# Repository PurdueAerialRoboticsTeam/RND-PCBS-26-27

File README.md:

2026-27 Git Repo for RND PCB designs. 25-26 reference designs available in archive

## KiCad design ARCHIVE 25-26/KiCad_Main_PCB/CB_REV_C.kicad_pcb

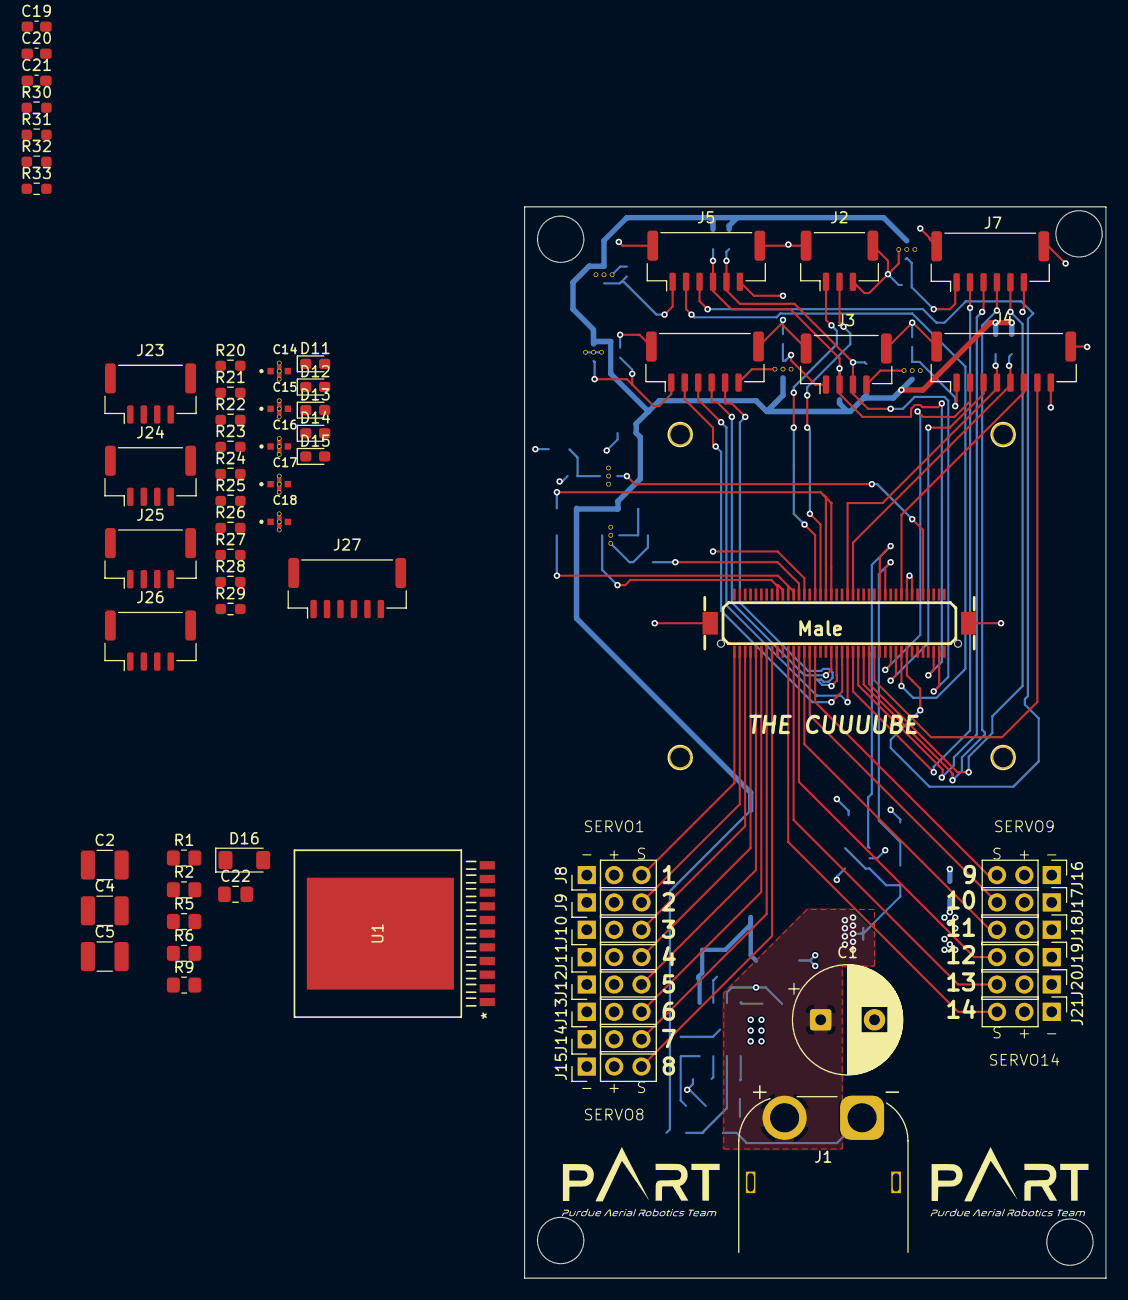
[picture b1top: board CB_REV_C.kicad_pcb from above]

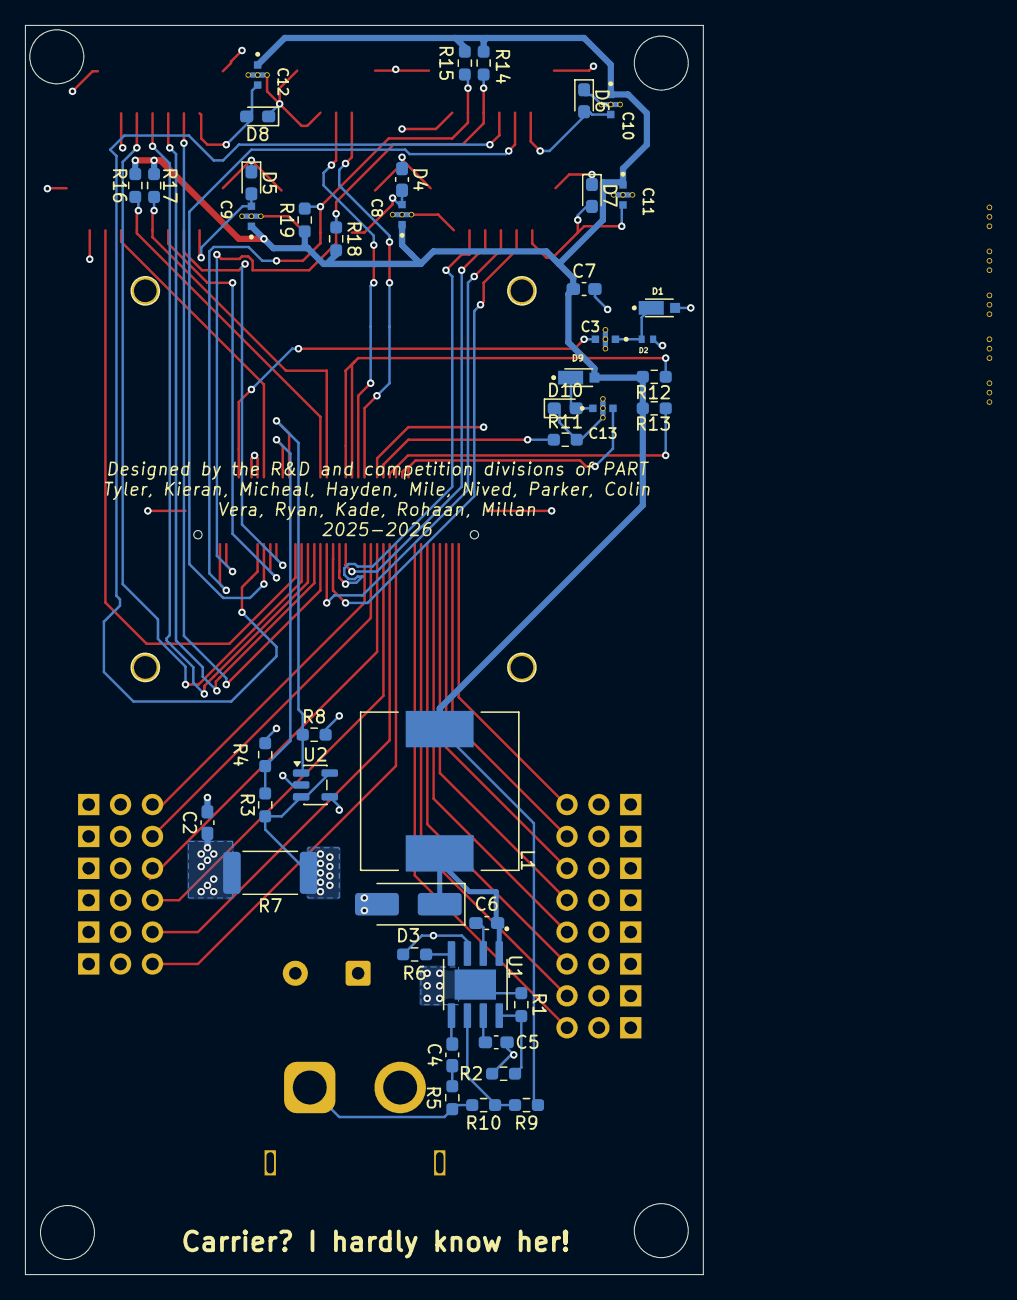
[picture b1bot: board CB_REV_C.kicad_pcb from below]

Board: 4 copper layers, 54.0 x 99.5 mm, 110 parts (44 on the bottom side), 70 nets.

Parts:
C1: 470u; CP_Radial_D10.0mm_P5.00mm
C2, C4, C5: 10uF; C_1210_3225Metric_Pad1.33x2.70mm_HandSolder
C2#2, C7: 10u; C_0603_1608Metric_Pad1.08x0.95mm_HandSolder
C3, C8, C9, C10, C11, C12, C13, C14, C15, C16, C17, C18: NFM18PC104R1C3D; FIL_NFM18PC104R1C3D
C4#2: 3n; C_0603_1608Metric_Pad1.08x0.95mm_HandSolder
C5#2, C6: 0.1u; C_0603_1608Metric_Pad1.08x0.95mm_HandSolder
C19, C20: 10uF 6.22 mOhm; C_0603_1608Metric_Pad1.08x0.95mm_HandSolder
C21: 47uF 2mOhm; C_0603_1608Metric_Pad1.08x0.95mm_HandSolder
C22: 0.47uF; C_0805_2012Metric_Pad1.18x1.45mm_HandSolder
D1, D9: MSS1P4-M3; MSS1P4-M3_89A
D2: PESD0603-240; PESD0402-140
D3: SS54; D_SMA_Handsoldering
D4: PESD0603-240; C_0603_1608Metric_Pad1.08x0.95mm_HandSolder
D5, D6, D7, D8, D11, D12, D13, D14, D15: PESD0603-240; D_0603_1608Metric_Pad1.05x0.95mm_HandSolder
D10: PESD0402-140; D_0603_1608Metric_Pad1.05x0.95mm_HandSolder
D16: BZV55B4V7; D_MiniMELF
J1: XT60; AMASS_XT60PW-M_1x02_P7.20mm_Horizontal
J2: Conn_01x03; JST_GH_BM03B-GHS-TBT_1x03-1MP_P1.25mm_Vertical
J3, J23, J24, J25, J26: Conn_01x04_MountingPin; JST_GH_BM04B-GHS-TBT_1x04-1MP_P1.25mm_Vertical
J4: Conn_01x08_MountingPin; JST_GH_BM08B-GHS-TBT_1x08-1MP_P1.25mm_Vertical
J5, J6, J7, J27: Conn_01x06_MountingPin; JST_GH_BM06B-GHS-TBT_1x06-1MP_P1.25mm_Vertical
J8, J9, J10, J11, J12, J13, J14, J15, J16, J17, J18, J19, J20, J21: Conn_01x03_Pin; PinHeader_1x03_P2.54mm_Vertical
J22: Cube80Pin; CON-DF17-80M
L1: 22u; L_12x12mm_H8mm
R1: 33 kOhm; R_0805_2012Metric_Pad1.20x1.40mm_HandSolder
R1#2, R2#2: 47k; R_0603_1608Metric_Pad0.98x0.95mm_HandSolder
R2: 10 kOhm; R_0805_2012Metric_Pad1.20x1.40mm_HandSolder
R3: 82K; R_0603_1608Metric_Pad0.98x0.95mm_HandSolder
R4: 47K; R_0603_1608Metric_Pad0.98x0.95mm_HandSolder
R5: 1.3k Ohm; R_0805_2012Metric_Pad1.20x1.40mm_HandSolder
R5#2: 43.7k; R_0603_1608Metric_Pad0.98x0.95mm_HandSolder
R6: 6.8k Ohm; R_0805_2012Metric_Pad1.20x1.40mm_HandSolder
R6#2: 46.4k; R_0603_1608Metric_Pad0.98x0.95mm_HandSolder
R7: 0.01; R_2512_6332Metric_Pad1.40x3.35mm_HandSolder
R8: 75k; R_0603_1608Metric_Pad0.98x0.95mm_HandSolder
R9: 100 Ohm; R_0805_2012Metric_Pad1.20x1.40mm_HandSolder
R9#2: 52.3k; R_0603_1608Metric_Pad0.98x0.95mm_HandSolder
R10, R14, R15, R16, R17, R18, R19, R20, R21, R22, R23, R24, R25, R26, R27, R28, R29, R33: 10k; R_0603_1608Metric_Pad0.98x0.95mm_HandSolder
R11, R12, R13: 100k; R_0603_1608Metric_Pad0.98x0.95mm_HandSolder
R30: 40.2 kOhm; R_0603_1608Metric_Pad0.98x0.95mm_HandSolder
R31: 4.42 kOhm; R_0603_1608Metric_Pad0.98x0.95mm_HandSolder
R32: 1.37K; R_0603_1608Metric_Pad0.98x0.95mm_HandSolder
U1: LMZ12008TZ/NOPB; TZA11A
U1#2: AOZ1284PI; SOP127P600X170-9N
U2: INA138; SOT-23-5

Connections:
+5V_SERVO: C7.1, C8.1, C9.1, C10.1, C11.1, C12.1, C14.1, C15.1, C16.1, C17.1, C18.1, C19.2, C20.2, C21.1, C21.2, D9.2 (A), L1.2, R6.1, R9#2.1, R12.1, R13.1, R14.2, R15.1, R16.2, R17.1, R18.2, R19.1, R20.2, R21.1, R22.2, R23.1, R24.2, R25.2, R26.1, R27.1, R28.2, R29.1, R33.1, U1.10 (VOUT), U1.11 (VOUT)
+BATT: C2.1, C2#2.1, C4.1, C5.1, C19.1, C20.1, D1.2 (A), J8.2, J9.2, J10.2, J11.2, J12.2, J13.2, J14.2, J15.2, J16.2, J17.2, J18.2, J19.2, J20.2, J21.2, J22.53, R1.1, R1#2.1, R7.2, U1.1 (VIN), U1.2 (VIN), U1#2.9 (VIN), U2.4 (-)
/80_Pin/FMU_CH1_PROT: J16.3, J22.50
/80_Pin/FMU_CH2_PROT: J17.3, J22.52
/80_Pin/FMU_CH3_PROT: J18.3, J22.54
/80_Pin/FMU_CH4_PROT: J19.3, J22.56
/80_Pin/FMU_CH5_PROT: J20.3, J22.58
/80_Pin/FMU_CH6_PROT: J21.3, J22.60
/80_Pin/IO_CH1_PROT: J8.3, J22.80
/80_Pin/IO_CH2_PROT: J9.3, J22.78
/80_Pin/IO_CH3_PROT: J10.3, J22.76
/80_Pin/IO_CH4_PROT: J11.3, J22.74
/80_Pin/IO_CH5_PROT: J12.3, J22.72
/80_Pin/IO_CH6_PROT: J13.3, J22.70
/80_Pin/IO_CH7_PROT: J14.3, J22.68
/80_Pin/IO_CH8_PROT: J15.3, J22.66
/80_Pin/VBUS_VALID: J22.57, J22.59, R13.2
/80_Pin/VDD_5V_HIPOWER_OC: J22.43, J22.45, R12.2
/80_Pin/VDD_5V_IN_PROT: C13.3, J22.61, J22.63
/80_Pin/VDD_BRICK_VALID: J22.55, R11.1
/BATT_MOT_A_MEAS: J2.1, J22.49
/BATT_MOT_V_MEAS: J2.2, J22.47
/BATT_SERVO_A_MEAS: J22.25, R8.1, U2.1
/BATT_SERVO_V_MEAS: J22.23, R3.2, R4.2
/I2C_1_SCL: J4.4, J22.37, J23.2, J24.2, J27.4, R16.1, R20.1, R22.1, R28.1
/I2C_1_SDA: J4.5, J22.35, J23.3, J24.3, J27.5, R17.2, R21.2, R23.2, R29.2
/I2C_2_SCL: J3.2, J5.4, J22.6, J25.2, J26.2, R14.1, R18.1, R24.1, R25.1
/I2C_2_SDA: J3.3, J5.5, J22.4, J25.3, J26.3, R15.2, R19.2, R26.2, R27.2
/SAFETY: J4.6, J22.17
/SERIAL1_CTS: J6.4, J22.44
/SERIAL1_RTS: J6.5, J22.42
/SERIAL1_RX: J6.3, J22.38
/SERIAL1_TX: J6.2, J22.40
/SERIAL2_CTS: J7.4, J22.32
/SERIAL2_RTS: J7.5, J22.30
/SERIAL2_RX: J7.3, J22.34
/SERIAL2_TX: J7.2, J22.36
/SERIAL3_RX: J4.3, J22.20
/SERIAL3_TX: J4.2, J22.22
/SERIAL4_RX: J5.3, J22.16
/SERIAL4_TX: J5.2, J22.18
/SERIAL5_RX: J22.12, J27.3
/SERIAL5_TX: J22.14, J27.2
/VDD_SERVO_IN: C3.3, J22.9
/~IO-LED_SAFET_PROT: J4.7, J22.28
Analog_GND: R30.2, R31.2, R32.2
GND: C1.2, C2.2, C2#2.2, C3.2, C4.2, C5.2, C5#2.2, C7.2, C8.2, C9.2, C10.2, C11.2, C12.2, C13.2, C14.2, C15.2, C16.2, C17.2, C18.2, C22.1, D2.1 (A1), D3.2 (A), D4.1 (A1), D5.1 (A1), D6.1 (A1), D7.1 (A1), D8.1 (A1), D10.1 (A1), D11.1 (A1), D12.1 (A1), D13.1 (A1), D14.1 (A1), D15.1 (A1), D16.2 (A), J1.1 (-), J2.3, J2.MP (MountPin), J3.4, J3.MP (MountPin), J4.8, J4.MP (MountPin), J5.6, J5.MP (MountPin), J6.6, J6.MP (MountPin), J7.6, J7.MP (MountPin), J8.1, J9.1, J10.1, J11.1, J12.1, J13.1, J14.1, J15.1, J16.1, J17.1, J18.1, J19.1, J20.1, J21.1, J22.13, J22.15, J22.GND, J23.4, J23.MP (MountPin), J24.4, J24.MP (MountPin), J25.4, J25.MP (MountPin), J26.4, J26.MP (MountPin), J27.6, J27.MP (MountPin), R2.1, R2#2.2, R4.1, R5.2, R5#2.2, R6#2.2, R8.2, R10.2, R11.2, U1.3 (AGND), U1.5 (AGND), U1.6 (AGND), U1.12 (PGND), U1#2.3 (GND), U2.2 (GND)
unnamed: C4#2.1, R5#2.1
unnamed: C3.1, D1.1 (K), D2.2 (A2)
unnamed: C6.2, D3.1 (K), L1.1, U1#2.1 (LX)
unnamed: C8.3, D4.2 (A2), J3.1
unnamed: C9.3, D5.2 (A2), J4.1
unnamed: C10.3, D6.2 (A2), J5.1
unnamed: C11.3, D7.2 (A2), J6.1
unnamed: C12.3, D8.2 (A2), J7.1
unnamed: C13.1, D9.1 (K), D10.2 (A2)
unnamed: C14.3, D11.2 (A2), J23.1
unnamed: C15.3, D12.2 (A2), J24.1
unnamed: C16.3, D13.2 (A2), J25.1
unnamed: C17.3, D14.2 (A2), J26.1
unnamed: C18.3, D15.2 (A2), J27.1
unnamed: D16.1 (K), R1.2, R2.2, R9.2
unnamed: C1.1, J1.2 (+), R3.1, R7.1, U2.3 (+), U2.5 (V+)
unnamed: C6.1, U1#2.2 (BST)
unnamed: C4#2.2, U1#2.5 (COMP)
unnamed: R1#2.2, R2#2.1, R9.1, U1.4 (EN), U1#2.8 (EN)
unnamed: R5.1, R6.2, R9#2.2, R10.1, U1.7 (FB), U1#2.6 (FB)
unnamed: R6#2.1, U1#2.4 (FSW)
unnamed: C5#2.1, C22.2, U1.8 (SS), U1#2.7 (SS)
unnamed: R32.1, R33.2
